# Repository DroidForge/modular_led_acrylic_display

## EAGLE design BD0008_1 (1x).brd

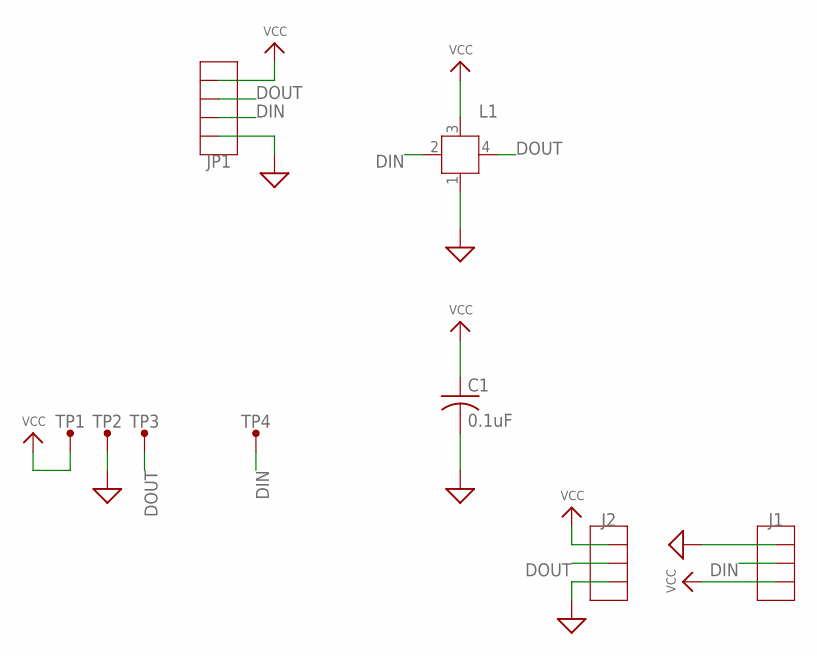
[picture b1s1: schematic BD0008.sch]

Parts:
C1: 0.1uF; C0402
J1: HEADER_1X3MALE; M3SMD
J2: HEADER_1X3FEMALE; F3SMD
JP1: HEADER_1X4S; 1X04
L1: WS2812B; SK6812
TP1: VCC; TEST_POINT
TP2: GND; TEST_POINT
TP3: DOUT; TEST_POINT
TP4: DIN; TEST_POINT

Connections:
DIN: J1.2, JP1.2, L1.2 (DIN), TP4.P$1
DOUT: J2.2A, J2.2B, JP1.3, L1.4 (DOUT), TP3.P$1
GND: C1.2, J1.1, J2.3A, J2.3B, JP1.1, L1.1 (VSS), TP2.P$1
VCC: C1.1, J1.3, J2.1A, J2.1B, JP1.4, L1.3 (VDD), TP1.P$1

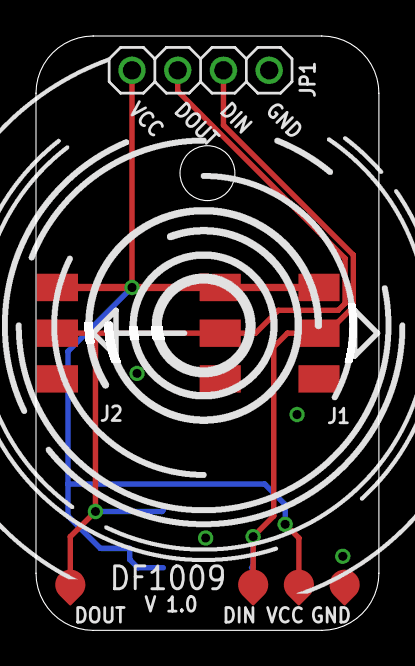
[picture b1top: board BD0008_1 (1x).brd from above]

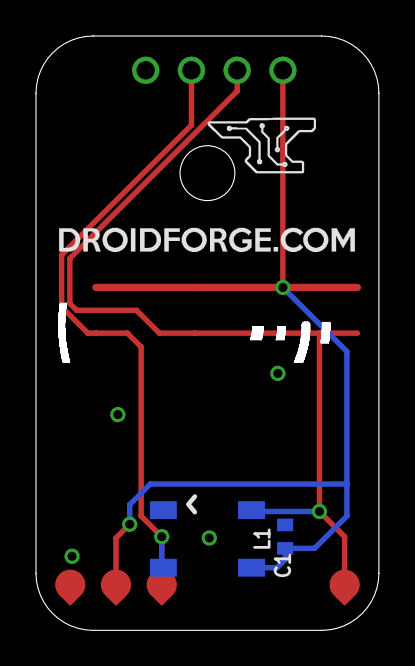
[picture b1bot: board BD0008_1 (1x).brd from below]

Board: 2 copper layers, 19.1 x 33.0 mm, 9 parts (2 on the bottom side), 4 nets.
